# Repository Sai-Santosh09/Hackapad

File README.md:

# Travel Navigation Macropad

## Overview

This project is a compact 4-key travel-themed macropad powered by the Seeed Studio XIAO RP2040. It features four directional navigation keys and two SK6812 MINI-E RGB LEDs. The project includes a custom PCB designed in KiCad, a custom enclosure designed in Fusion 360, and firmware developed using KMK.

## Features

* Seeed Studio XIAO RP2040
* 4 Mechanical Switches
* 2 SK6812 MINI-E RGB LEDs
* Compact 2-Layer PCB
* Custom Designed Enclosure
* KMK Firmware
* USB-C Connectivity

## Key Layout

* **8** → Up Arrow
* **6** → Right Arrow
* **4** → Left Arrow
* **2** → Down Arrow

The layout is inspired by classic numpad navigation controls to provide an intuitive travel and navigation experience.

## Design Process

After completing the PCB in KiCad, I verified the layout by checking component placement, USB connector alignment, mounting hole positions, and overall board dimensions. I then designed the top and bottom enclosure in Fusion 360 using the PCB as a reference, creating switch cutouts, screw holes, and the internal cavity. After verifying the enclosure dimensions, I exported the models as STEP files. Finally, I configured the KMK firmware by mapping the correct GPIO pins and assigning directional arrow key functions.

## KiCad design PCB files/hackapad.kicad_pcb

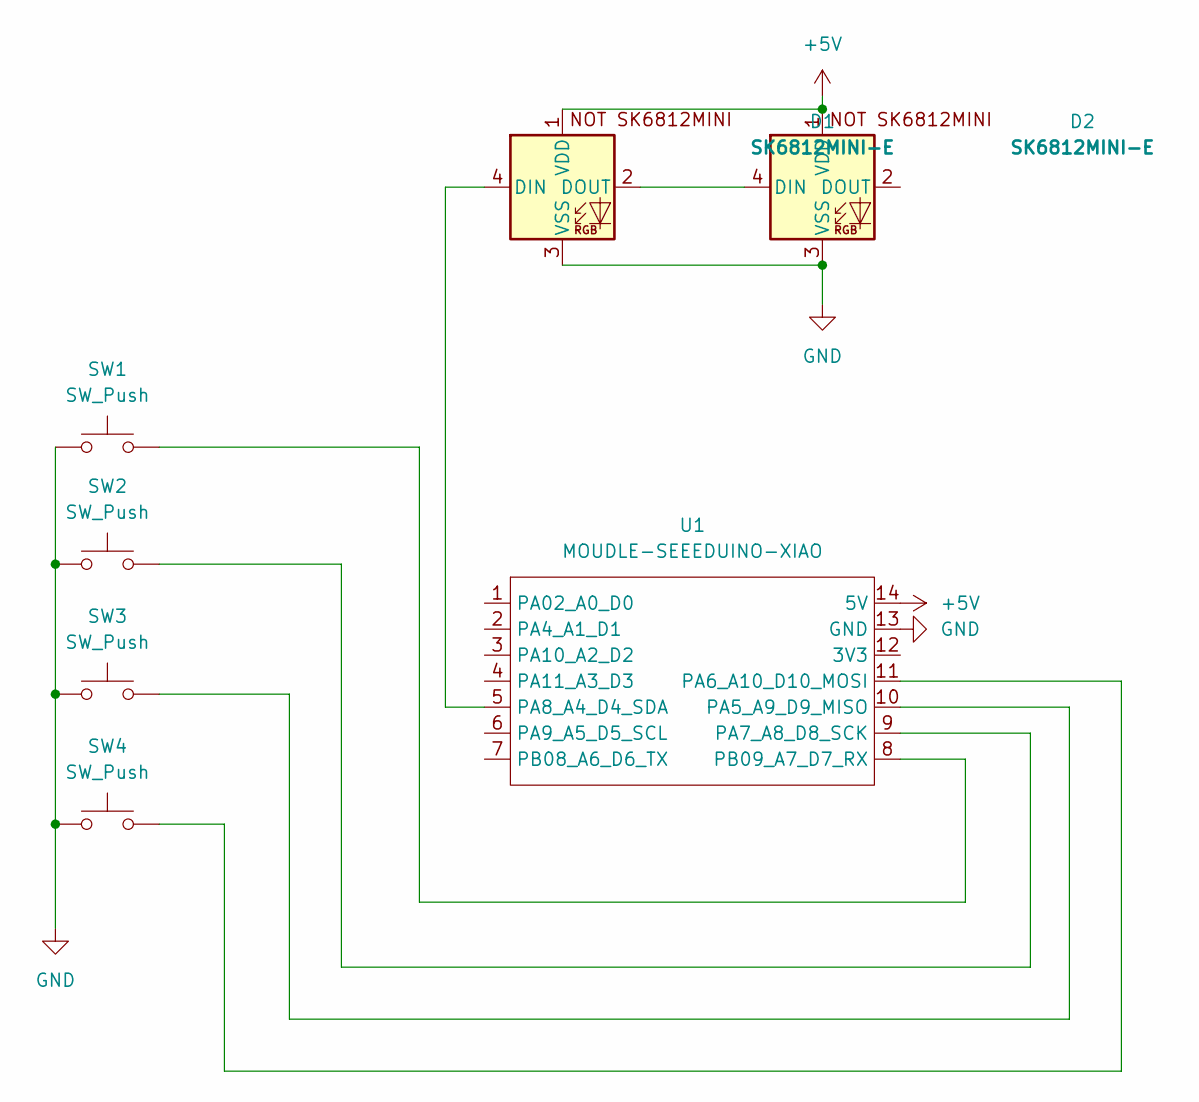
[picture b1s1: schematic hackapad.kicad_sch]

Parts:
D1, D2: SK6812MINI-E; SK6812MINI-E_fixed
SW1, SW2, SW3, SW4: SW_Push; SW_Cherry_MX_1.00u_PCB
U1: MOUDLE-SEEEDUINO-XIAO; XIAO-Generic-Hybrid-14P-2.54-21X17.8MM

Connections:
+5V: D1.1 (VDD), D2.1 (VDD), U1.14 (5V)
GND: D1.3 (VSS), D2.3 (VSS), SW1.1, SW2.1, SW3.1, SW4.1, U1.13 (GND)
unnamed: D1.4 (DIN), U1.5 (PA8_A4_D4_SDA)
unnamed: D1.2 (DOUT), D2.4 (DIN)
unnamed: SW3.2, U1.10 (PA5_A9_D9_MISO)
unnamed: SW4.2, U1.11 (PA6_A10_D10_MOSI)
unnamed: SW2.2, U1.9 (PA7_A8_D8_SCK)
unnamed: SW1.2, U1.8 (PB09_A7_D7_RX)

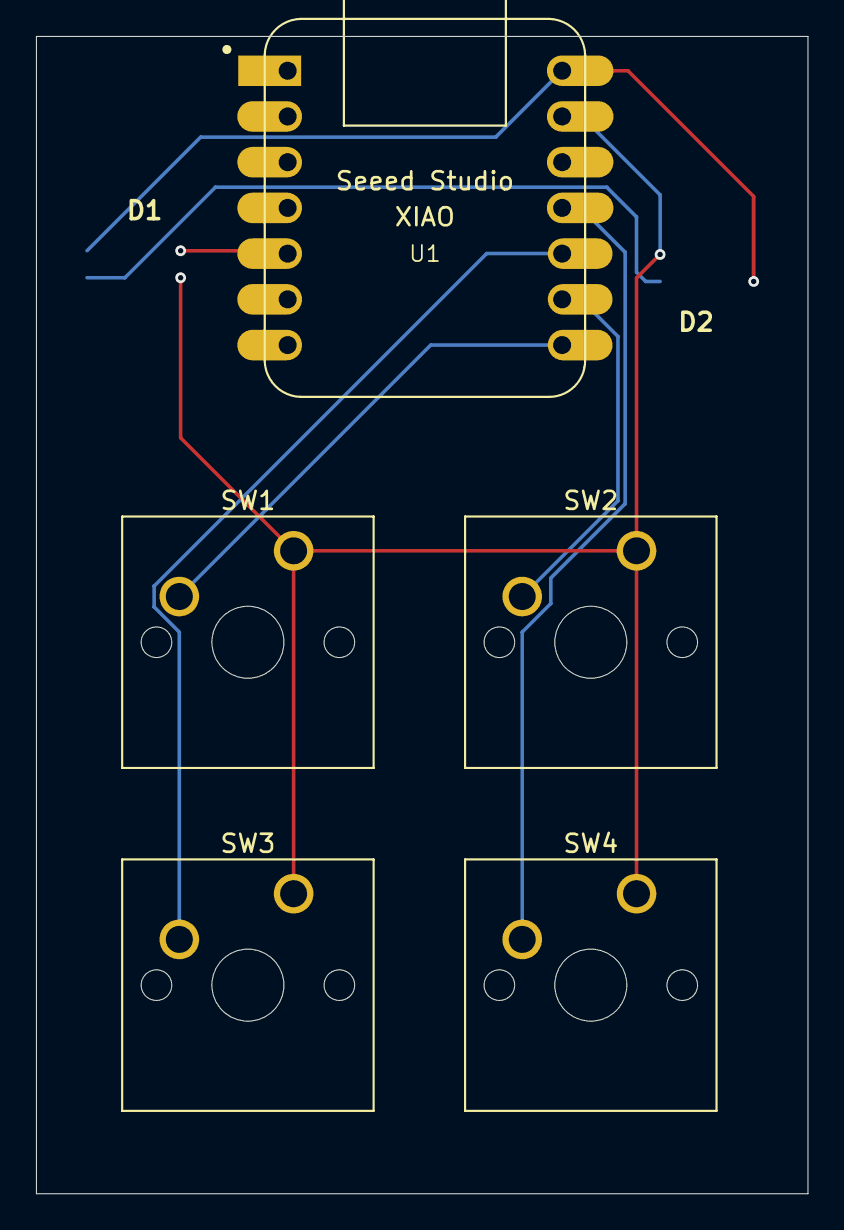
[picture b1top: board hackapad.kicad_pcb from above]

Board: 2 copper layers, 42.9 x 64.3 mm, 7 parts (0 on the bottom side), 8 nets.

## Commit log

2026-06-24 first commit of my harware project, completed the schematic and PCB design
2026-06-24 README with project details
    Added project overview, features, and key layout.
2026-06-26 added fusion360 STEP files and firmware
2026-06-26 README with project details and design process
    Final Readme
